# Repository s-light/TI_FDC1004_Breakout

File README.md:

# TI_FDC1004_Breakout
simple breakout board for TI FDC1004
(4 Channel Capacitance to Digital Converter for Capacitive Sensing Solutions)

You can find the datasheet at http://www.ti.com/product/fdc1004

the FDC1004 IOs are 3.3V only.  
for 5V compatibility the breakout has a 3.3V Regulator and
level-shifting for the I2C lines.

i have also written a [arduino library for this device](https://github.com/s-light/slight_FDC1004).

<!-- License info -->
<br />
<span xmlns:dct="http://purl.org/dc/terms/" property="dct:title">
    TI FDC1004 Breakout
</span> by
<a
    xmlns:cc="http://creativecommons.org/ns#"
    href="https://github.com/s-light/"
    property="cc:attributionName"
    rel="cc:attributionURL"
>
    Stefan Krüger (s-light)
</a>
is licensed under a<br/>
<a rel="license" href="http://creativecommons.org/licenses/by/4.0/">
    Creative Commons Attribution 4.0 International License
</a>.

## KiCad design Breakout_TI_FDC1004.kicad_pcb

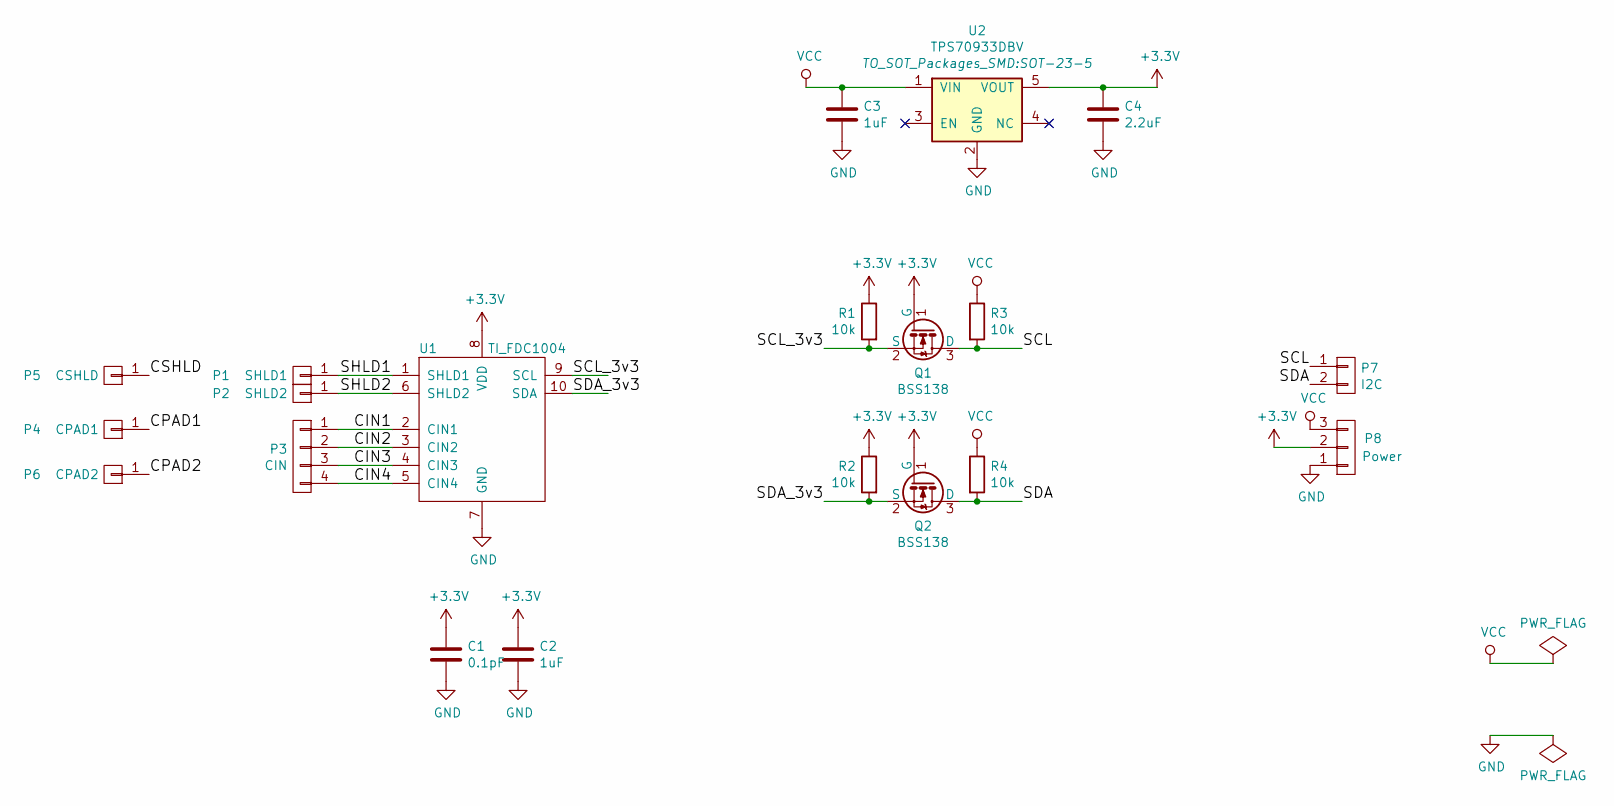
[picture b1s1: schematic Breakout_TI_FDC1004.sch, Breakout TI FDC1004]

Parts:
C1: 0.1pF; C_0805_HandSoldering
C2, C3: 1uF; C_0805_HandSoldering
C4: 2.2uF; C_0805_HandSoldering
P1: SHLD1; Pin_Header_Straight_1x01
P2: SHLD2; Pin_Header_Straight_1x01
P3: CIN; Pin_Header_Straight_1x04
P4: CPAD1; Pin_Header_Straight_1x01
P5: CSHLD; Pin_Header_Straight_1x01
P6: CPAD2; Pin_Header_Straight_1x01
P7: I2C; Pin_Header_Straight_1x02
P8: Power; Pin_Header_Straight_1x03
Q1, Q2: BSS138; SOT-23
R1, R2, R3, R4: 10k; R_0805_HandSoldering
U1: TI_FDC1004; MSOP-10_3x3mm_Pitch0.5mm
U2: TPS70933DBV; SOT-23-5

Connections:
+3V3: C1.1, C2.1, C4.1, P8.2, Q1.1 (G), Q2.1 (G), R1.1, R2.1, U1.8 (VDD), U2.5 (VOUT)
/CIN1: P3.1, U1.2 (CIN1)
/CIN2: P3.2, U1.3 (CIN2)
/CIN3: P3.3, U1.4 (CIN3)
/CIN4: P3.4, U1.5 (CIN4)
/CPAD1: P4.1
/CPAD2: P6.1
/CSHLD: P5.1
/SCL: P7.1, Q1.3 (D), R3.2
/SCL_3v3: Q1.2 (S), R1.2, U1.9 (SCL)
/SDA: P7.2, Q2.3 (D), R4.2
/SDA_3v3: Q2.2 (S), R2.2, U1.10 (SDA)
/SHLD1: P1.1, U1.1 (SHLD1)
/SHLD2: P2.1, U1.6 (SHLD2)
GND: C1.2, C2.2, C3.2, C4.2, P8.1, U1.7 (GND), U2.2 (GND)
VCC: C3.1, P8.3, R3.1, R4.1, U2.1 (VIN)

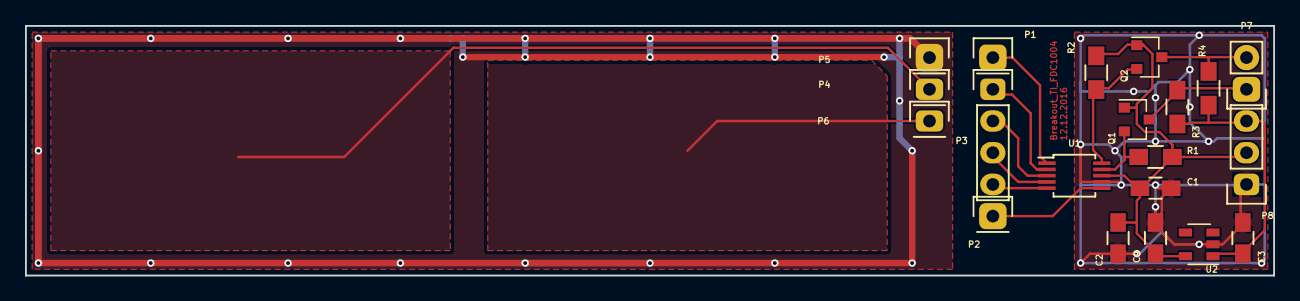
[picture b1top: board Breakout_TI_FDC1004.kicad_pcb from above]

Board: 2 copper layers, 100.0 x 20.0 mm, 20 parts (0 on the bottom side), 13 nets.

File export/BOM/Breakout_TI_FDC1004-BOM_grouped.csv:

Reference, Quantity, Value, Footprint, Datasheet
C1 ,1,0.1pF,Capacitors_SMD:C_0805_HandSoldering,
C2 C3 ,2,1uF,Capacitors_SMD:C_0805_HandSoldering,
C4 ,1,2.2uF,Capacitors_SMD:C_0805_HandSoldering,
P1 ,1,SHLD1,Pin_Headers:Pin_Header_Straight_1x01,
P2 ,1,SHLD2,Pin_Headers:Pin_Header_Straight_1x01,
P3 ,1,CIN,Pin_Headers:Pin_Header_Straight_1x04,
P4 ,1,CPAD1,Pin_Headers:Pin_Header_Straight_1x01,
P5 ,1,CSHLD,Pin_Headers:Pin_Header_Straight_1x01,
P6 ,1,CPAD2,Pin_Headers:Pin_Header_Straight_1x01,
P7 ,1,I2C,Pin_Headers:Pin_Header_Straight_1x02,
P8 ,1,Power,Pin_Headers:Pin_Header_Straight_1x03,
Q1 Q2 ,2,BSS138,TO_SOT_Packages_SMD:SOT-23,
R1 R2 R3 R4 ,4,10k,Resistors_SMD:R_0805_HandSoldering,
U1 ,1,TI_FDC1004,Housings_SSOP:MSOP-10_3x3mm_Pitch0.5mm,http://www.ti.com/lit/ds/symlink/fdc1004.pdf
U2 ,1,TPS70933DBV,TO_SOT_Packages_SMD:SOT-23-5,

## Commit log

2016-12-24 init
2016-12-25 improved readme

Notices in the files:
README.md:
<img alt="Creative Commons License" style="border-width:0"
src="https://i.creativecommons.org/l/by/4.0/88x31.png" />
